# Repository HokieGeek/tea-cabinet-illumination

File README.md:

# tea-cabinet-illumination

My very first circuit, not including those I built in college

# Schematics

# Board

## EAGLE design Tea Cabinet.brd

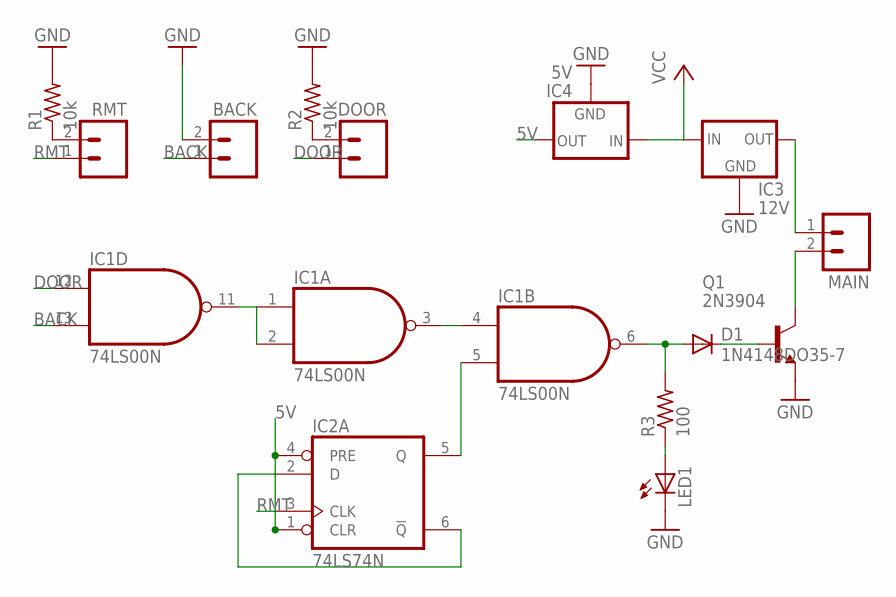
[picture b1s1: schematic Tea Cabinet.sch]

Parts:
BACK: M02PTH; 1X02
D1: 1N4148DO35-7; DO35-7
DOOR: M02PTH; 1X02
IC1: 74LS00N; DIL14
IC2: 74LS74N; DIL14
IC3: 12V; 78XXS
IC4: 5V; 78XXS
LED1: LED5MM
MAIN: M02PTH; 1X02
Q1: 2N3904; TO92
R1, R2: 10k; 0204/5
R3: 100; 0204/5
RMT: M02PTH; 1X02

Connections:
5V: IC2.1 (CLR), IC2.4 (PRE), IC4.OUT
12V: IC3.OUT, MAIN.1
BACK: BACK.1, IC1.13 (I1)
DOOR: DOOR.1, IC1.12 (I0)
GND: BACK.2, IC1.7 (GND), IC2.7 (GND), IC3.GND, IC4.GND, LED1.K (C), Q1.3 (E), R1.2, R2.2
unnamed: LED1.A, R3.1
unnamed: MAIN.2, Q1.1 (C)
unnamed: D1.C, Q1.2 (B)
unnamed: R1.1, RMT.2
unnamed: IC1.1 (I0), IC1.2 (I1), IC1.11 (O)
unnamed: D1.A, IC1.6 (O), R3.2
unnamed: DOOR.2, R2.1
unnamed: IC2.2 (D), IC2.6 (!Q)
unnamed: IC1.5 (I1), IC2.5 (Q)
unnamed: IC1.3 (O), IC1.4 (I0)
RMT: IC2.3 (CLK), RMT.1
VCC: IC1.14 (VCC), IC2.14 (VCC), IC3.IN, IC4.IN

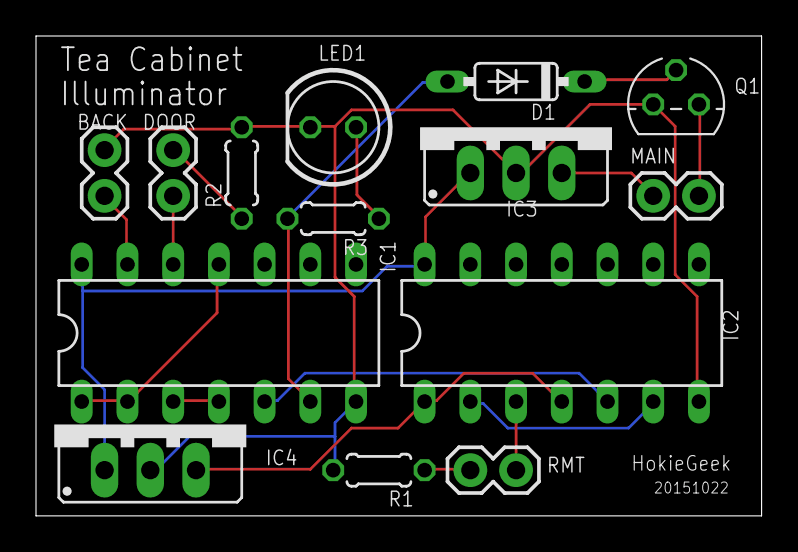
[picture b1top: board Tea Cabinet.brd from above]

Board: 2 copper layers, 40.3 x 26.7 mm, 14 parts (0 on the bottom side), 17 nets.

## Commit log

2015-10-16 Bringing into its own repo
2015-10-23 Made the board more compact
